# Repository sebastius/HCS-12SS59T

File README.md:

# HCS-12SS59T
Driverboard for the Samsung VFD HCS-12SS59T

Borrowed schematic from https://github.com/qrti/VFD-HCS-12SS59T

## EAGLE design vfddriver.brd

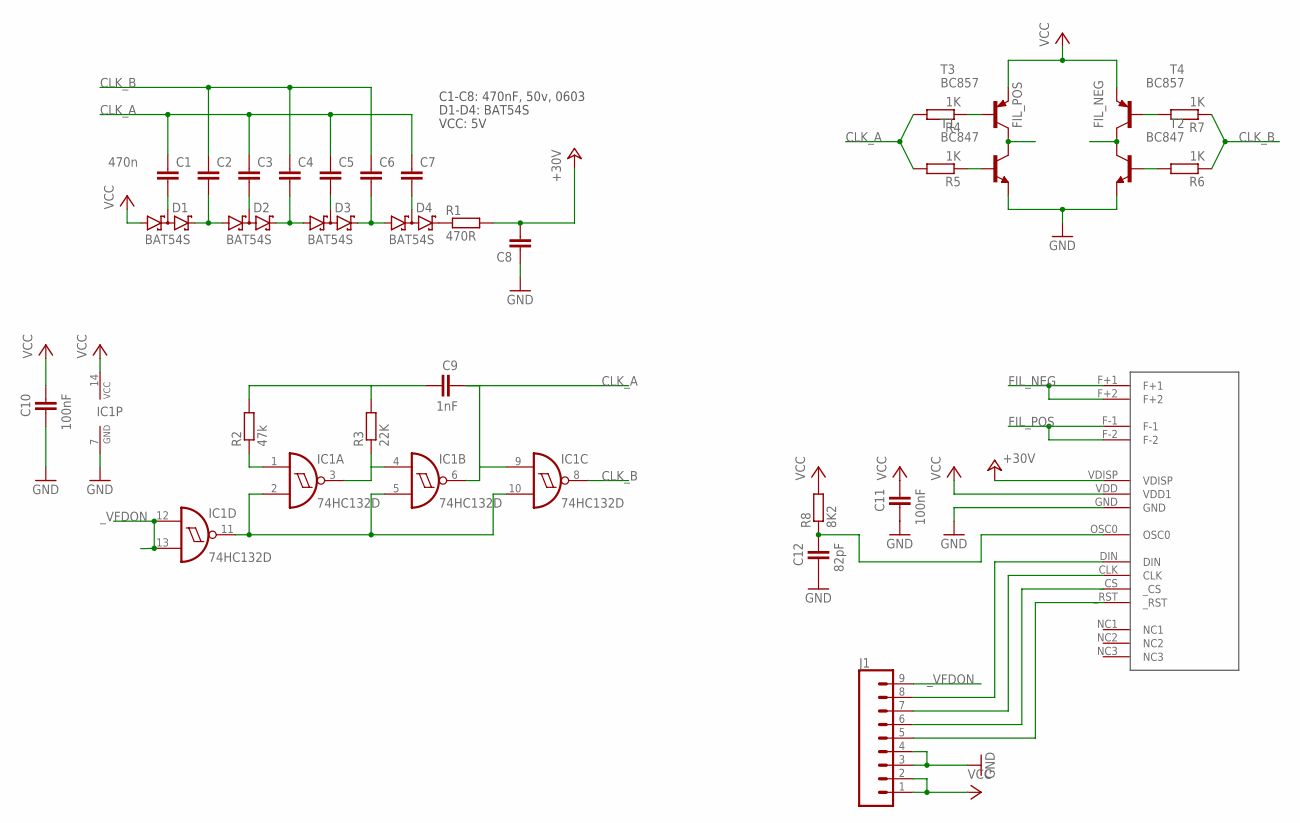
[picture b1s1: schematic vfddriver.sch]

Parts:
C1, C6, C8: 470n; C0603
C2, C3, C4, C5, C7: 470n 50v; C0603
C9: 1nF; C0603
C10, C11: 100nF; C0603
C12: 82pF; C0603
D1, D2, D3, D4: BAT54S; SOT23
IC1: 74HC132D; SO14
J1: CONN_09LONGPADS; 1X09_LONGPADS
R1: 470R; R0603
R2: 47k; R0603
R3: 22K; R0603
R4, R5, R6, R7: 1K; R0603
R8: 8K2; R0603
T1, T2: BC847; SOT23
T3, T4: BC857; SOT23-BEC
U$1: SAMSUNGHCS-12SS59T

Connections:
+24V: C8.2, R1.2, U$1.VDISP
CLK_A: C1.1, C3.1, C5.1, C7.1, C9.2, IC1.6 (O), IC1.9 (I0), R4.2, R5.2
CLK_B: C2.1, C4.1, C6.1, IC1.8 (O), R6.1, R7.1
FIL_NEG: T2.3 (C), T4.C, U$1.F+1, U$1.F+2
FIL_POS: T1.3 (C), T3.C, U$1.F-1, U$1.F-2
GND: C8.1, C10.1, C11.1, C12.1, IC1.7 (GND), J1.3, J1.4, T1.2 (E), T2.2 (E), U$1.GND
unnamed: C2.2, D1.2 (C2), D2.1 (A1)
unnamed: C4.2, D2.2 (C2), D3.1 (A1)
unnamed: C6.2, D3.2 (C2), D4.1 (A1)
unnamed: C5.2, D3.3 (C1A2)
unnamed: D4.2 (C2), R1.1
unnamed: C1.2, D1.3 (C1A2)
unnamed: C3.2, D2.3 (C1A2)
unnamed: C7.2, D4.3 (C1A2)
unnamed: R4.1, T3.B
unnamed: IC1.1 (I0), R2.1
unnamed: C9.1, R2.2, R3.2
unnamed: IC1.3 (O), IC1.4 (I0), R3.1
unnamed: R5.1, T1.1 (B)
unnamed: R7.2, T4.B
unnamed: R6.2, T2.1 (B)
unnamed: C12.2, R8.1, U$1.OSC0
unnamed: J1.8, U$1.DIN
unnamed: IC1.2 (I1), IC1.5 (I1), IC1.10 (I1), IC1.11 (O)
unnamed: J1.7, U$1.CLK
unnamed: J1.6, U$1._CS
unnamed: J1.5, U$1._RST
VCC: C10.2, C11.2, D1.1 (A1), IC1.14 (VCC), J1.1, J1.2, R8.2, T3.E, T4.E, U$1.VDD (VDD1)
_VFDON: IC1.12 (I0), IC1.13 (I1), J1.9

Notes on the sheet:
C1-C8: 470nF, 50v, 0603
D1-D4: BAT54S
VCC: 5V

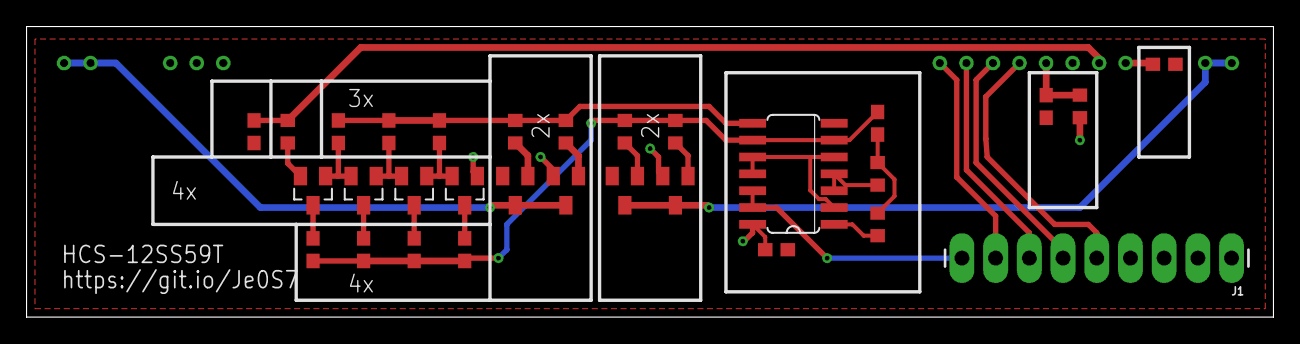
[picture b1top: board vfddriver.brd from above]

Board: 2 copper layers, 94.0 x 21.9 mm, 31 parts (1 on the bottom side), 29 nets.

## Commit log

2019-10-24 First version
2019-10-24 Datasheet
    Might contain errors. Dunno.

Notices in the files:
parts and their libraries:
SparkFun-Connectors: Licensing: Creative Commons ShareAlike 4.0 International - https://creativecommons.org/licenses/by-sa/4.0
